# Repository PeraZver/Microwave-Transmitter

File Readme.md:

# Microwave Transmitter

30 - 6000 MHz 10 dBm Transmitter based on MAX2871 synthesizer. 
Controlled by Teensy 3.2. 

![MW-Tx][3d]

Some parts of the circuit design based on H. Forsten's home made VNA. The microwave transmitter consists of following blocks:

 * **Synthesizer** is based on MAX2871 chip (PLL with integrated VCO) and its loop filter. This guy is able to synthesize frequencies from 25 MHz to 6 GHz.
 * **Filter bank** that makes sure no harmonics are generated in GHz range.
 * **Amplification** block that uses programmable attenuation for the gain control and 12 dB power amplifier TRF37A75.
 * **Coupler and RSSI detectors** that measure emitted and reflected power, of course. 
 * **Teensy 3.2** that controls the synthesizer, selects filter switches, controls the attenuation and AD converts measured power from the RSSI detectors and sends all of data to PC. 
 * **Power supply** that scales 12V input to 5V, 3.6V, 3.3V and 1.8V. 

User's guide of Microwave Transmitter is available at [Github repo's wiki](https://github.com/PeraZver/Microwave-Transmitter/wiki).

Development log of the Microwave Transmitter is documented at [Hackaday.io](https://hackaday.io/project/20350-microwave-transmitter).

Pero, February 2017
(https://www.helentronica.com)

[3d]: https://github.com/PeraZver/Microwave-Transmitter/blob/master/HW/Transmitter.jpg

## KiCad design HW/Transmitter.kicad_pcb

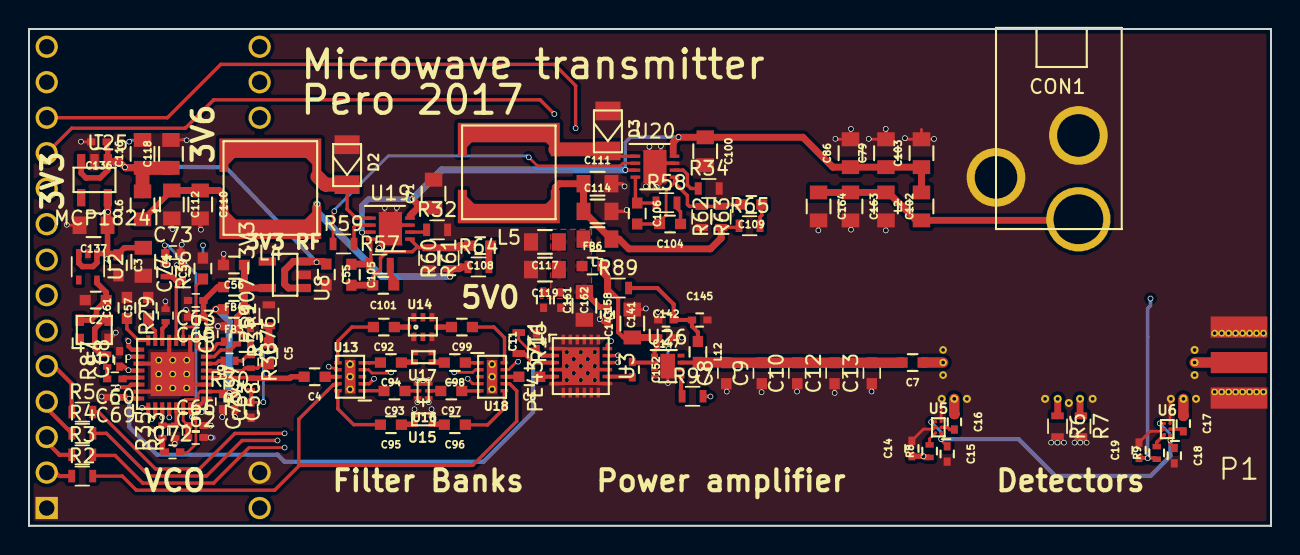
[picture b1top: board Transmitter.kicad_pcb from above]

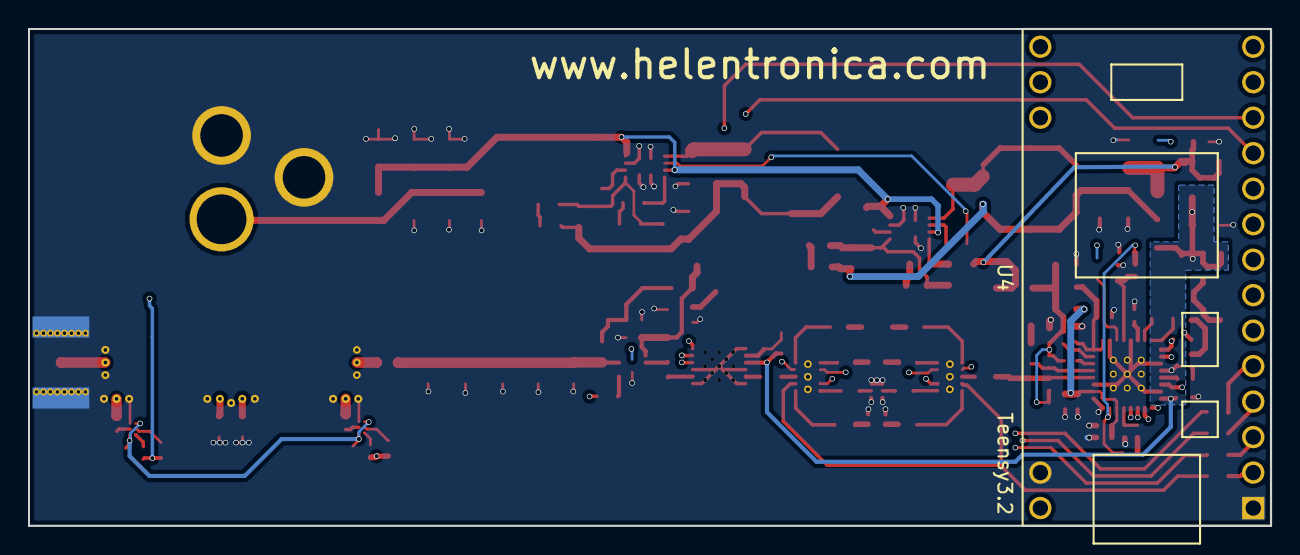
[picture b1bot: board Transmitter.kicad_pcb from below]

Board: 4 copper layers, 88.9 x 35.6 mm, 144 parts (2 on the bottom side), 98 nets.

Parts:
C1, C79, C86, C158, C163, C164: DNP; C_0805b
C2, C55, C56, C57, C59, C61: 1u; C_0603b
C3: 100n; C_0603b
C4, C5, C6, C7, C95, C96: 1n; C_0603b
C8, C9, C10, C12, C13: C; C_0603
C11, C14, C15, C18, C19, C136, C141, C142: 100n; C_0402b
C16, C17, C152: 1n; C_0402b
C58, C62, C63, C65, C68, C69, C72: 100n; C_0402
C60: 10n; C_0402
C64, C66, C67, C75, C76: 100p; C_0402
C71, C100, C102, C103, C110, C111, C112, C114, C116, C117, C118, C119, C137, C143: 10u; C_0805b
C73: 12n; C_0402
C74: 820p; C_0402
C92, C93, C97, C99: 10p; C_0603b
C94, C98, C105: 100p; C_0603b
C101, C104, C109: 10n; C_0603b
C106: 68p; C_0603b
C108: 4.7n; C_0603b
C145: 10p; C_0402b
C147: 10n; C_0402b
C161, C162: DNP; C_0402b
CON1: BARREL_JACK; EJ508A
D2, D3: SS13FL; SOD-123F
F3: COUPLER; coupler4
FB3, FB4, FB6: BLM18PG181SN1D; C_0603b
L2, L6, L7: 1u; C_0805b
L4: 33u (SRR6040A-330M); SRR6040A
L5: 100u (SRR6040A-101M); SRR6040A
L12: LQW18ANR10J00D; C_0603b
P1: SMA; CONSMA003.062
R1, R6, R7: 49.9; R_0603
R2, R3, R4, R5, R16: 33; R_0603
R8, R9: 100; R_0402b
R29: 5.1k; R_0402
R30, R31, R87: 0; R_0402
R32, R34: 59k; R_0603
R33: 90.9; R_0402
R35: 30.1; R_0402
R36: 240; R_0402
R37, R38: 49.9; R_0402
R57: 6.8k; R_0603
R58: 8.2k; R_0603
R59: 0; R_0603
R60, R62: 4.99k; R_0603
R61: 1k; R_0603
R63: 680; R_0603
R64, R97: 100; R_0603
R65: 56; R_0603
R89: 1.8; R_0603
U1: ASTXR-12-19.200MHz; ASTRX-12
U2: MIC5366; SOT-353_SC-70-5
U3: PE43711; VQFN-24
U4: Teensy3.2; Teensy30_31_32_LC
U5, U6: LMH2110; WFBGA-6
U8: LP5907-3V3; SOT-23-5
U9: MAX2871; TQFN-32
U13, U18: SKY13322-375LF; MLPD-10
U14: 5515LP15A730
U15: LP0603A0902ANTR; LP0603A0902
U16: 3550LP14A300
U17: LP0603A1880ANTR; LP0603A0902
U19, U20: L7980; DFN-8-1EP_3x3mm_Pitch0.5mm
U25: MCP1824T; SOT-23-5
U26: TRF37A75; DFN-8-1EP_2x2mm_Pitch0.5mm

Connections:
/1V8: C2.1, U1.6, U2.5
/3V3: C1.1, C3.1, C68.1, C69.1, C137.1, R16.2, U2.1, U2.3, U3.3, U9.28, U9.32, U25.5
/3V6: C55.1, C116.1, C118.1, C136.1, L6.2, U8.1, U8.3, U25.1, U25.3
/5V: C117.1, C119.1, C141.1, C158.1, C161.1, C162.1, FB6.1, L7.2
/ADC_A: C19.1, R9.1, U4.21
/ADC_B: C14.1, R8.1, U4.22
/ATT_LE: U3.16, U4.12
/CLK_REF: R87.2, U1.4
/FILTER_V1: R4.2, U13.4, U18.2
/FILTER_V2: R3.2, U13.2, U18.4
/FILTER_V3: R5.2, U13.7, U18.9
/FILTER_V4: R2.2, U13.9, U18.7
/Filter Bank/RF_IN: C4.1, U13.8
/Filter Bank/RF_OUT: C6.2, U18.8
/PWDN: R97.2, U4.11
/Power Amplifier/PA5V: C142.1, C143.1, FB6.2, R89.1, U26.1
/Power Amplifier/RF_IN: C6.1, U3.5
/Power Amplifier/RF_OUT: C7.2, C8.2, C9.2, C10.2, C12.2, C13.2, L12.2, U26.7
/Power Supply/12V: C71.1, C79.1, C86.1, C100.1, C103.1, L2.2, U19.3, U19.8, U20.3, U20.8
/Power Supply/12V_IN: C102.1, C163.1, C164.1, CON1.1, L2.1
/Power Supply/SYNC_3V3: R59.2, U19.2
/Power Supply/SYNC_5V: R59.1, U20.2
/RF Detectors/3V3: C15.1, C18.1, U5.A1, U5.C2, U6.A1, U6.C2
/RF Detectors/A: C17.1, F3.6
/RF Detectors/B: C16.1, F3.3
/RF Detectors/RF_IN: C7.1, F3.1
/RF Detectors/RF_OUT: F3.2, P1.1
/SOURCE_CE: U4.6, U9.4
/SOURCE_LD: U4.10, U9.25
/SOURCE_LE: U4.7, U9.3
/SOURCE_MUXOUT: U4.8, U9.30
/SOURCE_RF_ENABLE: U4.9, U9.26
/SPI_CLK: U3.17, U4.20, U9.1
/SPI_DATA: U3.18, U4.13, U9.2
/VCO/3V3_PLL: C58.1, C62.1, C64.1, C66.1, FB3.2, U9.6, U9.10
/VCO/3V3_RF: C56.1, C75.2, C76.2, FB3.1, FB4.1, R30.1, R31.1, R37.1, R38.1, U8.5
/VCO/RF_OUT_N: C5.2, R38.2, U9.13
/VCO/RF_OUT_P: C4.2, R37.2, U9.12
GND: C1.2, C2.2, C3.2, C8.1, C9.1, C10.1, C11.2, C12.1, C13.1, C14.2, C15.2, C18.2, C19.2, C55.2, C56.2, C57.2, C58.2, C59.2, C61.2, C62.2, C63.2, C64.2, C65.2, C66.2, C67.2, C68.2, C69.2, C71.2, C73.2, C74.2, C75.1, C76.1, C79.2, C86.2, C100.2, C102.2, C103.2, C110.2, C111.2, C112.2, C114.2, C116.2, C117.2, C118.2, C119.2, C136.2, C137.2, C141.2, C142.2, C143.2, C145.2, C147.2, C158.2, C161.2, C162.2, C163.2, C164.2, CON1.2, CON1.3, D2.2, D3.2, F3.GND, P1.2, R1.2, R6.2, R7.2, R29.2, R32.2, R33.1, R34.2, R61.2, R63.2, U1.3, U2.2, U3.1, U3.4, U3.6, U3.7, U3.8, U3.9, U3.10, U3.11, U3.12, U3.13, U3.15, U3.19, U3.20, U3.21, U3.22, U3.23, U3.24, U3.EP, U4.1, U4.32, U5.B2, U5.C1, U6.B2, U6.C1, U8.2, U9.8, U9.9, U9.11, U9.18, U9.21, U9.27, U9.31, U9.EP, U13.EP, U14.1, U14.3, U14.5, U14.7, U15.3, U15.4, U16.1, U16.3, U16.4, U16.6, U17.3, U17.4, U18.EP, U19.7, U19.9, U20.7, U20.9, U25.2, U26.9
unnamed: C5.1, R1.1
unnamed: C11.1, R16.1, U3.2
unnamed: C16.2, U5.B1
unnamed: C17.2, U6.B1
unnamed: C57.1, U9.23
unnamed: C59.1, U9.19
unnamed: C60.1, U9.29
unnamed: C60.2, R87.1
unnamed: C61.1, U9.24
unnamed: C63.1, C65.1, C67.1, FB4.2, U9.16, U9.17
unnamed: C72.1, R35.1
unnamed: C72.2, C73.1, R36.1, U9.7
unnamed: C74.1, R36.2, U9.20
unnamed: C92.1, U14.8
unnamed: C92.2, U13.6
unnamed: C93.1, U16.2
unnamed: C93.2, U13.1
unnamed: C94.1, U17.1
unnamed: C94.2, U13.5
unnamed: C95.1, U15.1
unnamed: C95.2, U13.10
unnamed: C96.1, U18.6
unnamed: C96.2, U15.2
unnamed: C97.1, U18.5
unnamed: C97.2, U16.5
unnamed: C98.1, U18.1
unnamed: C98.2, U17.2
unnamed: C99.1, U18.10
unnamed: C99.2, U14.4
unnamed: C101.1, R57.2
unnamed: C101.2, C105.2, C108.2, R60.2, R61.1, U19.5
unnamed: C104.1, R58.2
unnamed: C104.2, C106.2, C109.2, R62.2, R63.1, U20.5
unnamed: C105.1, R57.1, U19.4
unnamed: C106.1, R58.1, U20.4
unnamed: C108.1, R64.2
unnamed: C109.1, R65.2
unnamed: C110.1, C112.1, L4.2, L6.1, R60.1, R64.1
unnamed: C111.1, C114.1, L5.2, L7.1, R62.1, R65.1
unnamed: C145.1, C147.1, L12.1, R89.2
unnamed: C152.1, U26.2
unnamed: C152.2, U3.14
unnamed: D2.1, L4.1, U19.1
unnamed: D3.1, L5.1, U20.1
unnamed: F3.4, R6.1
unnamed: F3.5, R7.1
unnamed: R2.1, U4.2
unnamed: R3.1, U4.3
unnamed: R4.1, U4.4
unnamed: R5.1, U4.5
unnamed: R8.2, U5.A2
unnamed: R9.2, U6.A2
unnamed: R29.1, U9.22
unnamed: R30.2, U9.14
unnamed: R31.2, U9.15
unnamed: R32.1, U19.6
unnamed: R33.2, R35.2, U9.5
unnamed: R34.1, U20.6
unnamed: R97.1, U26.5

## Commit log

2017-07-22 initial commit of SW
2017-07-22 add hw design files
2017-07-23 Started working with temperature read.
2017-07-25 added .h library
2017-07-26 fixed temp & vtune readout
2017-07-26 SPI init separate function
2017-07-27 made cpp file and test for filter switch
2017-08-09 tested all components and made basic example
2017-08-10 improved basic example; made MWtx lib; made register parser program
2017-08-11 basic example furnished
2017-08-11 add filter selection from serial terminal
2017-08-17 started with PlatformIO
2017-08-19 add power control over serial
2017-08-20 char array input for power and filter selection
2017-09-05 Added frequency control in UI (N, F, DIVA). Testted and verified
2017-09-06 small pyhton program to control serial terminal
2017-09-06 tweaking spaces for serial communication
2017-09-11 python console and sweep script
2017-09-12 added register parser in python script
2017-09-13 implemented sweep in firmware
2017-09-16 freq calculation
2017-09-17 help menu in python script
2017-09-17 from user interface select frequency
2017-09-23 improved Help menu
2017-09-24 add sweep program
2017-09-24 renamed folder Test to Firmware
2017-10-15 added attenuation control
